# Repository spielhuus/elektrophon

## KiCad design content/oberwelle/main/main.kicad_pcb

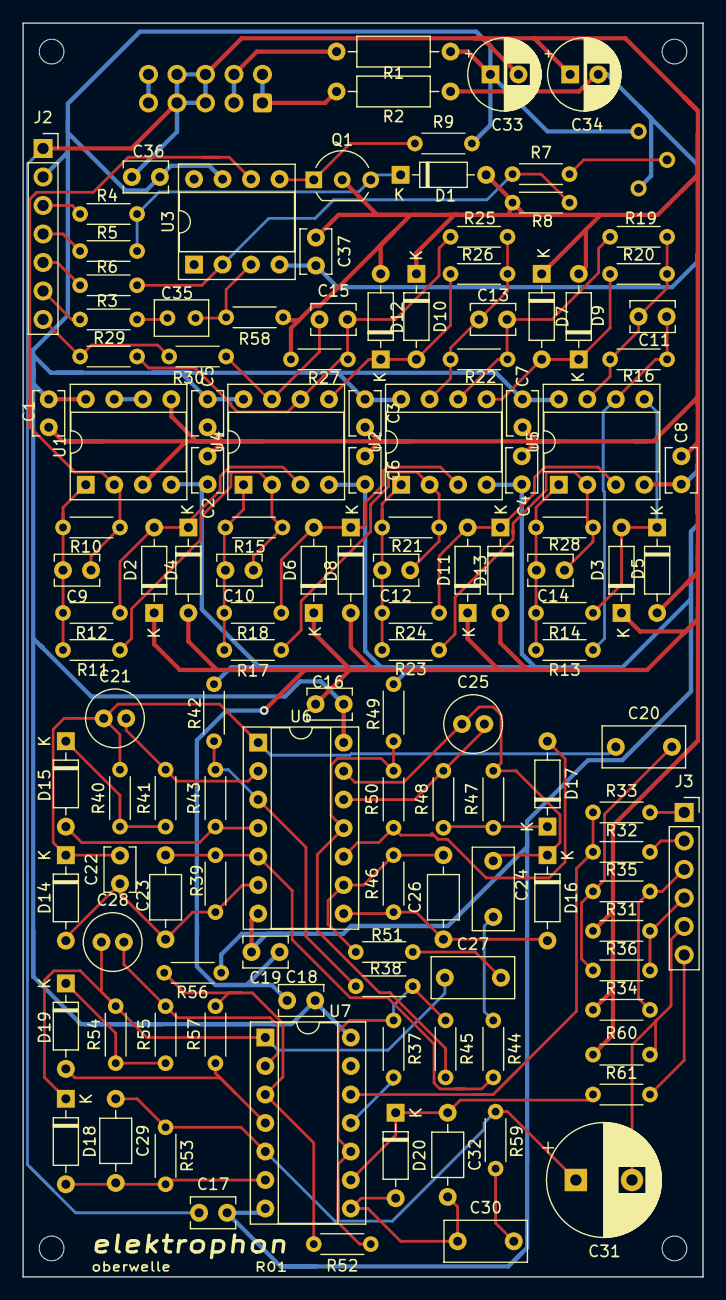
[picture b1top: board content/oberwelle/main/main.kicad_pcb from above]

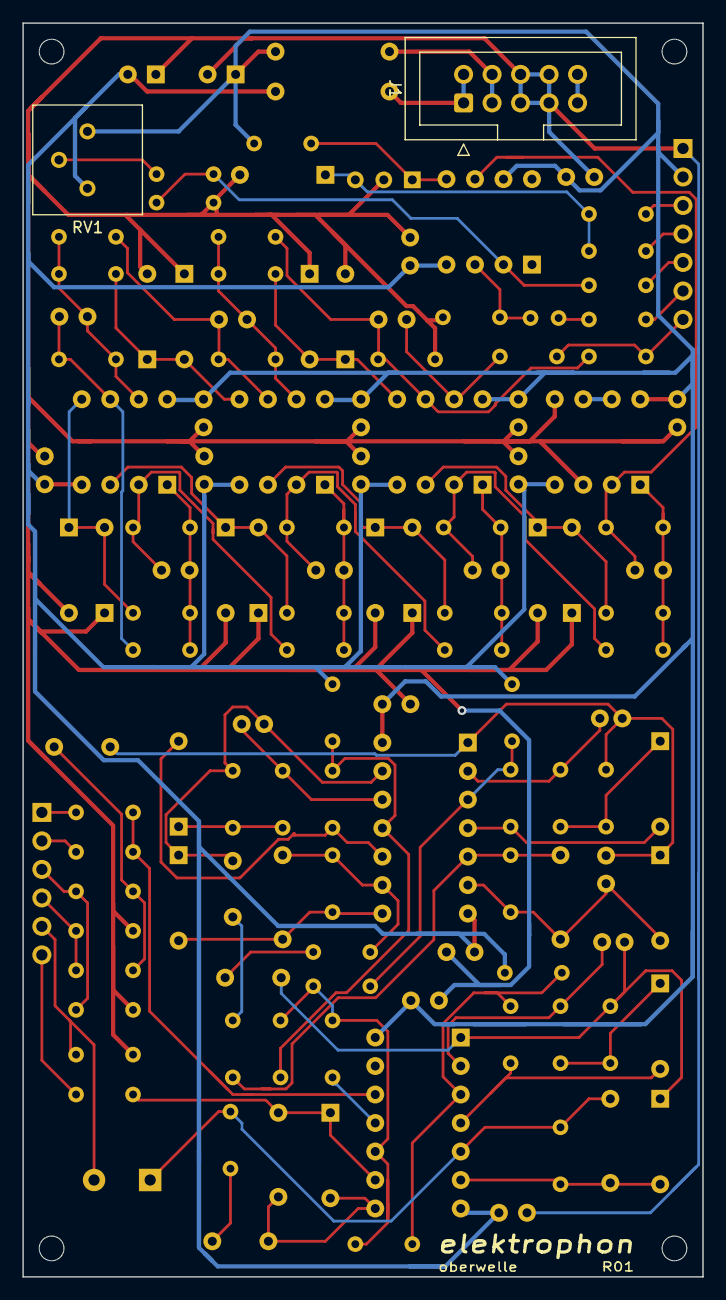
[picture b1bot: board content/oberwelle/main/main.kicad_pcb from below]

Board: 2 copper layers, 60.6 x 111.8 mm, 134 parts (2 on the bottom side), 74 nets.

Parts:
C1, C2, C3, C4, C5, C6, C7, C8, C16, C17, C18, C19, C36, C37: 0.1u; C_Disc_D3.8mm_W2.6mm_P2.50mm
C9: 150p; C_Disc_D3.8mm_W2.6mm_P2.50mm
C10, C11, C12, C13, C14, C15, C22: 47p; C_Disc_D3.8mm_W2.6mm_P2.50mm
C20, C24, C27, C30: 47n; C_Rect_L7.2mm_W3.5mm_P5.00mm_FKS2_FKP2_MKS2_MKP2
C21, C25, C28: 1u (BP); C_Radial_D5.0mm_H11.0mm_P2.00mm
C23, C26, C29, C32: 30p; C_Axial_L3.8mm_D2.6mm_P7.50mm_Horizontal
C31: 47u (BP); CP_Radial_D10.0mm_P5.00mm
C33, C34: 22u; CP_Radial_D6.3mm_P2.50mm
C35: 220n; C_Rect_L4.6mm_W3.0mm_P2.50mm_MKS02_FKP02
D1, D2, D3, D4, D5, D6, D7, D8, D9, D10, D11, D12, D13, D14, D15, D16, D17, D18, D19: 1N4148; D_DO-35_SOD27_P7.62mm_Horizontal
D20: 4.3V/400mW; D_DO-35_SOD27_P7.62mm_Horizontal
J1: IDC Header; IDC-Header_2x05_P2.54mm_Vertical
J2: Conn_01x07_Female; PinSocket_1x07_P2.54mm_Vertical
J3: Conn_01x06_Female; PinSocket_1x06_P2.54mm_Vertical
Q1: BC557; TO-92_Inline_Wide
R1, R2: 10; R_Axial_DIN0207_L6.3mm_D2.5mm_P10.16mm_Horizontal
R3, R6, R11, R13, R15, R16, R17, R19, R21, R22, R23, R25, R28, R29, R31, R33, R34, R59, R60: 100k; R_Axial_DIN0204_L3.6mm_D1.6mm_P5.08mm_Horizontal
R4: 47k; R_Axial_DIN0204_L3.6mm_D1.6mm_P5.08mm_Horizontal
R5: 15k; R_Axial_DIN0204_L3.6mm_D1.6mm_P5.08mm_Horizontal
R7: 3.3meg; R_Axial_DIN0204_L3.6mm_D1.6mm_P5.08mm_Horizontal
R8, R58: 1.5k; R_Axial_DIN0204_L3.6mm_D1.6mm_P5.08mm_Horizontal
R9: 6.8meg; R_Axial_DIN0204_L3.6mm_D1.6mm_P5.08mm_Horizontal
R10: 82k; R_Axial_DIN0204_L3.6mm_D1.6mm_P5.08mm_Horizontal
R12, R14, R18, R20, R24, R26: 33k; R_Axial_DIN0204_L3.6mm_D1.6mm_P5.08mm_Horizontal
R27: 10k; R_Axial_DIN0204_L3.6mm_D1.6mm_P5.08mm_Horizontal
R30: 330; R_Axial_DIN0204_L3.6mm_D1.6mm_P5.08mm_Horizontal
R32, R38: 220k; R_Axial_DIN0204_L3.6mm_D1.6mm_P5.08mm_Horizontal
R35, R36, R43, R44, R51: 1meg; R_Axial_DIN0204_L3.6mm_D1.6mm_P5.08mm_Horizontal
R37: 150k; R_Axial_DIN0204_L3.6mm_D1.6mm_P5.08mm_Horizontal
R39, R46, R53, R57: 2.2meg; R_Axial_DIN0204_L3.6mm_D1.6mm_P5.08mm_Horizontal
R40, R41, R47, R48, R54, R55: 10meg; R_Axial_DIN0204_L3.6mm_D1.6mm_P5.08mm_Horizontal
R42, R49, R56: 820k; R_Axial_DIN0204_L3.6mm_D1.6mm_P5.08mm_Horizontal
R45: 330k; R_Axial_DIN0204_L3.6mm_D1.6mm_P5.08mm_Horizontal
R50: 1.5meg; R_Axial_DIN0204_L3.6mm_D1.6mm_P5.08mm_Horizontal
R52: 470k; R_Axial_DIN0204_L3.6mm_D1.6mm_P5.08mm_Horizontal
R61: 3.3k; R_Axial_DIN0204_L3.6mm_D1.6mm_P5.08mm_Horizontal
REF1, REF2, REF3, REF4: MountingHole_2.2mm_M2
RV1: 100k; Potentiometer_Bourns_3386P_Vertical
U1, U2, U4, U5: TL072; DIP-8_W7.62mm_Socket
U3: CA3080; DIP-8_W7.62mm_Socket
U6, U7: LM3900; DIP-14_W7.62mm_Socket

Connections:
+5V: J1.9, J1.10
+15V: C1.1, C3.1, C5.1, C7.1, C16.1, C18.1, C33.1, C36.1, J2.2, R1.1, R9.2, RV1.1, U1.8, U2.8, U3.7, U4.8, U5.8, U6.14, U7.14
-15V: C2.2, C4.2, C6.2, C8.2, C17.2, C19.2, C34.2, C37.2, R2.1, R42.1, R49.1, R56.1, RV1.3, U1.4, U2.4, U3.4, U4.4, U5.4, U6.7, U7.7
CV: J3.1, R33.2
CV_INITIAL: J3.2, R32.2
GND: C1.2, C2.1, C3.2, C4.1, C5.2, C6.1, C7.2, C8.1, C16.2, C17.1, C18.2, C19.1, C33.2, C34.1, C36.2, C37.1, D1.2, D2.1, D3.1, D4.2, D5.2, D6.1, D7.1, D8.2, D9.2, D10.1, D11.1, D12.2, D13.2, J1.5, J1.6, J1.7, J1.8, J2.1, Q1.2, R8.1, R27.1, R31.1, R34.1, R58.1, R60.1, U1.3, U1.5
IN_1: J3.3, R34.2, R35.2
IN_2: J3.4, R31.2, R36.2
M_CV: J2.4, R5.2
M_CV_INITIAL: J2.3, R4.2
M_IN_1: J2.6, R3.2
M_IN_2: J2.5, R6.2
M_OUT: J2.7, R29.1, R30.1
unnamed: C9.1, R10.1, R11.2, R12.2, U1.1
unnamed: C9.2, R10.2, U1.2, U3.6
unnamed: C10.1, R15.1, R17.2, R18.2, U4.1
unnamed: C10.2, R11.1, R15.2, U4.2
unnamed: C11.1, R16.1, R19.2, R20.2, U5.7
unnamed: C11.2, R13.1, R16.2, U5.6
unnamed: C12.1, R21.1, R23.2, R24.2, U2.1
unnamed: C12.2, R17.1, R21.2, U2.2
unnamed: C13.1, R22.1, R25.2, R26.2, U2.7
unnamed: C13.2, R19.1, R22.2, U2.6
unnamed: C14.1, R13.2, R14.2, R28.1, U5.1
unnamed: C14.2, R23.1, R28.2, U5.2
unnamed: C15.1, R30.2, U4.7
unnamed: C15.2, R25.1, R27.2, R29.2, U4.6
unnamed: C20.1, C21.1, C22.2, D14.1, R40.2, U6.1
unnamed: C20.2, R35.1, R36.1
unnamed: C21.2, R41.2, U6.2
unnamed: C22.1, C23.2, D14.2, R39.2, U6.6
unnamed: C23.1, R39.1, R44.2, U6.5
unnamed: C24.1, C25.1, D16.1, R47.2, U6.13
unnamed: C24.2, R44.1
unnamed: C25.2, R48.2, U6.12
unnamed: C26.1, R46.1, R51.2, U6.9
unnamed: C26.2, D16.2, R46.2, U6.8
unnamed: C27.1, C28.1, D18.1, R54.2, U7.1
unnamed: C27.2, R51.1
unnamed: C28.2, R55.2, U7.2
unnamed: C29.1, C31.1, R53.1, R59.2, U7.5
unnamed: C29.2, D18.2, R53.2, U7.6
unnamed: C30.1, C32.2, D20.2, U7.8
unnamed: C30.2, R59.1
unnamed: C32.1, D20.1, R61.1, U7.9
unnamed: C35.1, R58.2, U3.3
unnamed: C35.2, R3.1
unnamed: D1.1, Q1.3, R4.1, R5.1
unnamed: D2.2, D4.1, R12.1, U4.3
unnamed: D3.2, D5.1, R14.1, U5.5
unnamed: D6.2, D8.1, R18.1, U2.3
unnamed: D7.2, D9.1, R20.1, U2.5
unnamed: D10.2, D12.1, R26.1, U4.5
unnamed: D11.2, D13.1, R24.1, U5.3
unnamed: D15.1, R40.1, R41.1
unnamed: D15.2, R43.1, U6.4
unnamed: D17.1, R47.1, R48.1
unnamed: D17.2, R50.1, U6.10
unnamed: D19.1, R54.1, R55.1
unnamed: D19.2, R57.1, U7.4
unnamed: Q1.1, R9.1, U3.5
unnamed: R6.1, R7.1, R8.2, U3.2
unnamed: R7.2, RV1.2
unnamed: R32.1, R33.1, U7.12
unnamed: R37.1, R38.1, R45.1, R52.1, U7.10
unnamed: R37.2, U7.11
unnamed: R38.2, R42.2, R43.2, U6.3
unnamed: R45.2, R49.2, R50.2, U6.11
unnamed: R52.2, R56.2, R57.2, U7.3
unnamed: U1.6, U1.7
OUT_1: C31.2, J3.5, R60.2
OUT_2: J3.6, R61.2
VN: J1.1, J1.2, R2.2
VP: J1.3, J1.4, R1.2

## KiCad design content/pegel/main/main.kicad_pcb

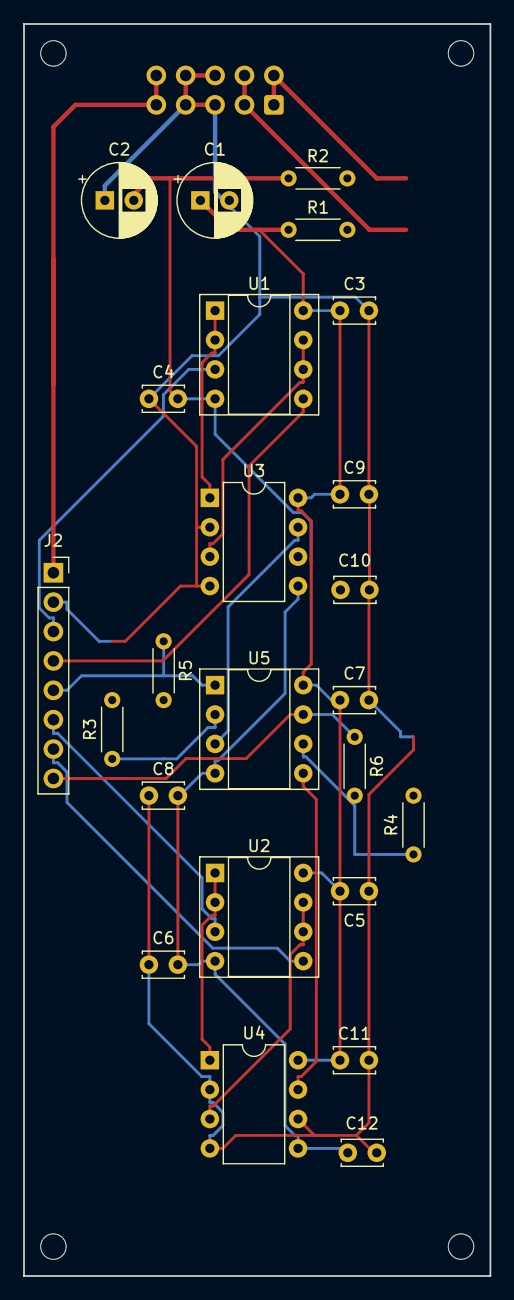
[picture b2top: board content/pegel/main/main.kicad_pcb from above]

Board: 2 copper layers, 40.3 x 108.2 mm, 29 parts (1 on the bottom side), 20 nets.

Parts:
C1, C2: 22u; CP_Radial_D6.3mm_P2.50mm
C3, C4, C5, C6, C7, C8, C9, C10, C11, C12: 0.1u; C_Disc_D3.4mm_W2.1mm_P2.50mm
H1, H2, H3, H4: MountingHole; MountingHole_2.2mm_M2
J1: IDC Header; IDC-Header_2x05_P2.54mm_Vertical
J2: Conn_01x08_Female; PinSocket_1x08_P2.54mm_Vertical
R1, R2: 10; R_Axial_DIN0204_L3.6mm_D1.6mm_P5.08mm_Horizontal
R3, R4, R5, R6: 10k; R_Axial_DIN0204_L3.6mm_D1.6mm_P5.08mm_Horizontal
U1, U2, U5: OPA2134; DIP-8_W7.62mm_Socket
U3, U4: AD633; DIP-8_W7.62mm

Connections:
+5V: J1.9, J1.10, J2.1
+15V: C1.1, C3.1, C5.1, C7.1, C9.1, C11.1, R1.1, U1.8, U2.8, U3.8, U4.8, U5.8
-15V: C2.2, C4.2, C6.2, C8.2, C10.2, C12.2, R2.1, U1.4, U2.4, U3.5, U4.5, U5.4
GND: C1.2, C2.1, C3.2, C4.1, C5.2, C6.1, C7.2, C8.1, C9.2, C10.1, C11.2, C12.1, J1.5, J1.6, J1.7, J1.8, J2.2, R3.2, R4.2, U3.2, U3.4, U3.6, U4.2, U4.4, U4.6
unnamed: R3.1, R5.2, U5.2
unnamed: R4.1, R6.2, U5.6
unnamed: U1.1, U1.2, U3.1
unnamed: U1.6, U1.7, U3.3
unnamed: U2.1, U2.2, U4.1
unnamed: U2.6, U2.7, U4.3
unnamed: U3.7, U5.3
unnamed: U4.7, U5.5
OUTa: J2.5, R5.1, U5.1
OUTb: J2.8, R6.1, U5.7
VN: J1.1, J1.2, R2.2
VP: J1.3, J1.4, R1.2
Xa: J2.3, U1.3
Xb: J2.6, U2.3
Ya: J2.4, U1.5
Yb: J2.7, U2.5

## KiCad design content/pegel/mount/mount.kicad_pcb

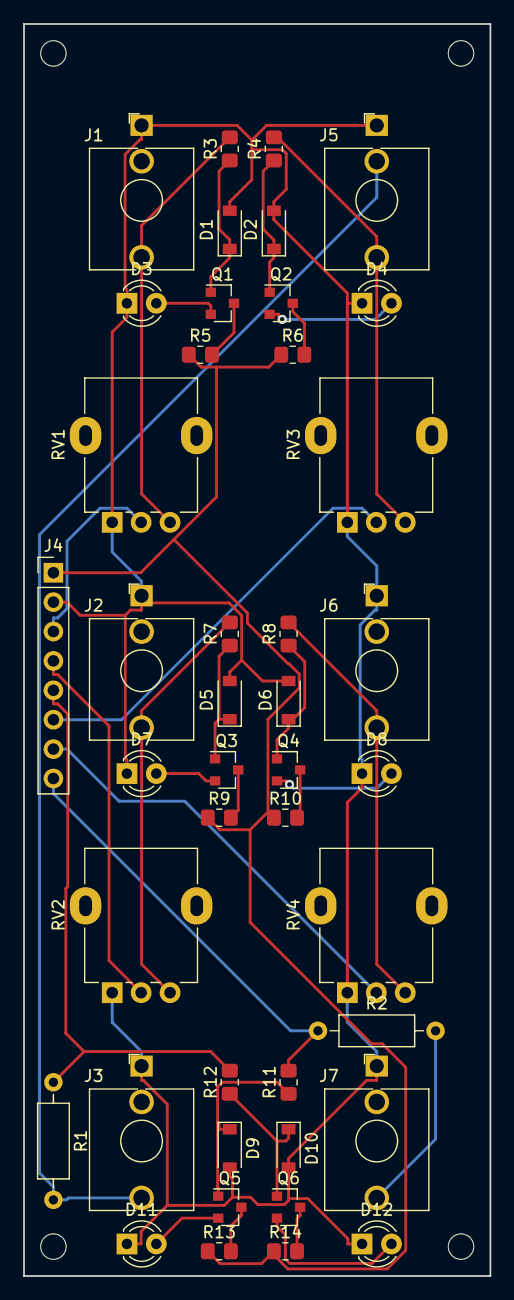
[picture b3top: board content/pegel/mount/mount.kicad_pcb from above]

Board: 2 copper layers, 40.3 x 108.2 mm, 47 parts (0 on the bottom side), 32 nets.

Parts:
D1, D2, D5, D6, D9, D10: 1N4148W; D_SOD-123
D3, D4, D7, D8, D11, D12: LED; LED_D3.0mm
H1, H2, H3, H4: MountingHole; MountingHole_2.2mm_M2
J1, J5: IN_X; Jack_3.5mm_WQP-PJ398SM_Vertical
J2, J6: IN_Y; Jack_3.5mm_WQP-PJ398SM_Vertical
J3, J7: OUT; Jack_3.5mm_WQP-PJ398SM_Vertical
J4: Conn_01x08_Male; PinHeader_1x08_P2.54mm_Vertical
Q1, Q2, Q3, Q4, Q5, Q6: MMBT3904; SOT-23
R1, R2: 1k; R_Axial_DIN0207_L6.3mm_D2.5mm_P10.16mm_Horizontal
R3, R4, R7, R8, R11, R12: 100k; R_0805_2012Metric_Pad1.20x1.40mm_HandSolder
R5, R6, R9, R10, R13, R14: 5k; R_0805_2012Metric_Pad1.20x1.40mm_HandSolder
RV1, RV2, RV3, RV4: 100k; Potentiometer_Alpha_RD901F-40-00D_Single_Vertical

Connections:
+5V: J4.1, R5.1, R6.1, R9.1, R10.1, R13.1, R14.1
/IN1x: J1.T, R3.2, RV1.3
/IN1y: J2.T, R7.2, RV2.3
/IN2x: J5.T, R4.2, RV3.3
/IN2y: J6.T, R8.2, RV4.3
GND: D1.2, D2.2, D3.1, D4.1, D5.2, D6.2, D7.1, D8.1, D9.2, D10.2, D11.1, D12.1, J1.S, J2.S, J3.S, J4.2, J5.S, J6.S, J7.S, RV1.1, RV2.1, RV3.1, RV4.1
unnamed: D1.1, Q1.1, R3.1
unnamed: D2.1, Q2.1, R4.1
unnamed: D3.2, Q1.2
unnamed: D4.2, Q2.2
unnamed: D5.1, Q3.1, R7.1
unnamed: D6.1, Q4.1, R8.1
unnamed: D7.2, Q3.2
unnamed: D8.2, Q4.2
unnamed: D9.1, Q5.1, R11.1
unnamed: D10.1, Q6.1, R12.1
unnamed: D11.2, Q5.2
unnamed: D12.2, Q6.2
unnamed: J3.T, J5.TN, R1.2
unnamed: J7.T, R2.2
unnamed: Q1.3, R5.2
unnamed: Q2.3, R6.2
unnamed: Q3.3, R9.2
unnamed: Q4.3, R10.2
unnamed: Q5.3, R13.2
unnamed: Q6.3, R14.2
OUTa: J4.5, R1.1, R12.2
OUTb: J4.8, R2.1, R11.2
Xa: J4.3, RV1.2
Xb: J4.6, RV3.2
Ya: J4.4, RV2.2
Yb: J4.7, RV4.2

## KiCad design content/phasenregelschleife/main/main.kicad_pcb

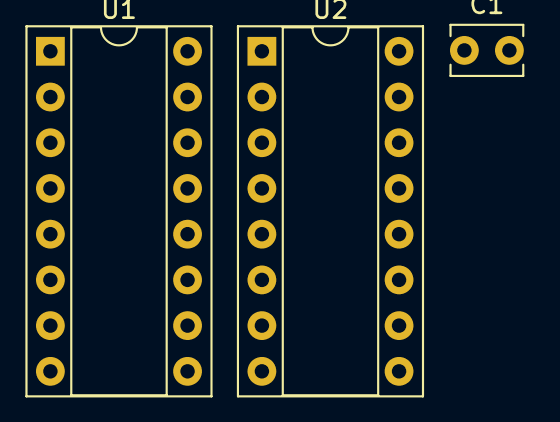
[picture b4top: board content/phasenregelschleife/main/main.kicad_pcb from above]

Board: 2 copper layers, 3 parts (0 on the bottom side), 3 nets, no tracks yet.

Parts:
C1: 0.01u; C_Disc_D3.8mm_W2.6mm_P2.50mm
U1, U2: 4046; DIP-16_W7.62mm_Socket

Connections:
GND: U1.5, U1.8
unnamed: C1.1, U1.6
unnamed: C1.2, U1.7

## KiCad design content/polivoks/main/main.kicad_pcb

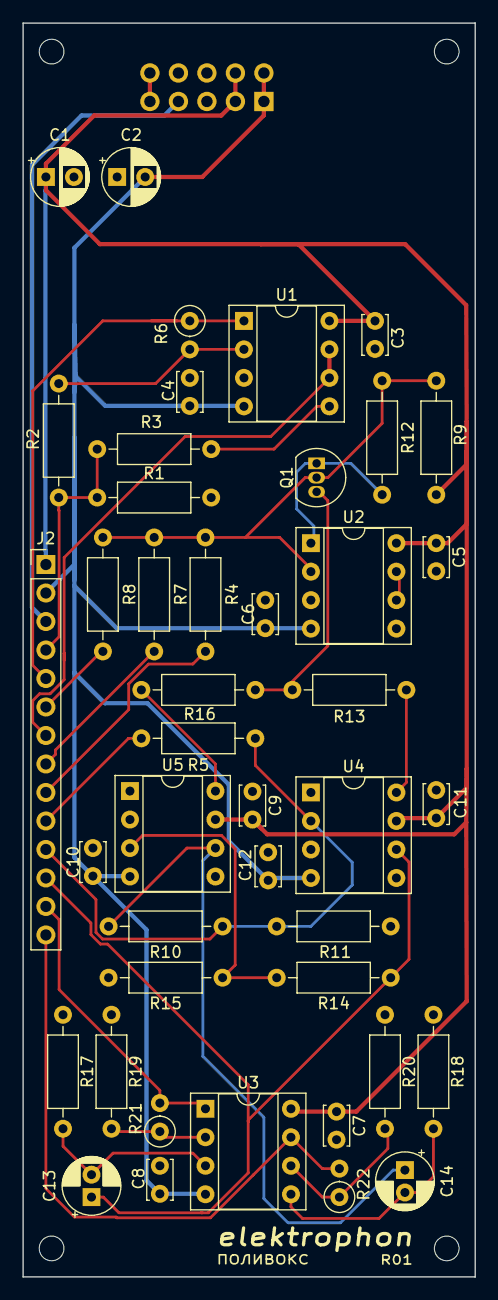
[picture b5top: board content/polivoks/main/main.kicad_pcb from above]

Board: 2 copper layers, 40.3 x 111.8 mm, 48 parts (1 on the bottom side), 29 nets.

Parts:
C1, C2: 10u; CP_Radial_D5.0mm_P2.50mm
C3, C4, C5, C6, C7, C8, C9, C10, C11, C12: 0.1u; C_Disc_D3.4mm_W2.1mm_P2.50mm
C13, C14: 1u; CP_Radial_D5.0mm_P2.00mm
H1, H2, H3, H4: MountingHole; MountingHole_2.2mm_M2
J1: IDC Header; IDC-Header_2x05_P2.54mm_Vertical
J2: Conn_01x14_Female; PinHeader_1x14_P2.54mm_Vertical
Q1: 2N3904; TO-92_Inline
R1: 220k; R_Axial_DIN0207_L6.3mm_D2.5mm_P10.16mm_Horizontal
R2, R4, R9, R17, R18: 100k; R_Axial_DIN0207_L6.3mm_D2.5mm_P10.16mm_Horizontal
R3, R19, R20: 10k; R_Axial_DIN0207_L6.3mm_D2.5mm_P10.16mm_Horizontal
R5: 470k; R_Axial_DIN0207_L6.3mm_D2.5mm_P10.16mm_Horizontal
R6, R21, R22: 100k; R_Axial_DIN0207_L6.3mm_D2.5mm_P2.54mm_Vertical
R7: 162k; R_Axial_DIN0207_L6.3mm_D2.5mm_P10.16mm_Horizontal
R8: 120k; R_Axial_DIN0207_L6.3mm_D2.5mm_P10.16mm_Horizontal
R10, R14: 47k; R_Axial_DIN0207_L6.3mm_D2.5mm_P10.16mm_Horizontal
R11, R15: 1k; R_Axial_DIN0207_L6.3mm_D2.5mm_P10.16mm_Horizontal
R12: 3k; R_Axial_DIN0207_L6.3mm_D2.5mm_P10.16mm_Horizontal
R13, R16: 1M2; R_Axial_DIN0207_L6.3mm_D2.5mm_P10.16mm_Horizontal
U1, U2, U3: TL072; DIP-8_W7.62mm_Socket
U4, U5: LM4250; DIP-8_W7.62mm_Socket

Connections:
+5V: J1.9, J1.10
+15V: C1.1, C3.1, C5.1, C7.1, C9.1, C11.1, J1.3, J1.4, J2.1, R9.2, U1.8, U2.8, U3.8, U4.7, U5.7
-15V: C2.2, C4.2, C6.2, C8.2, C10.2, C12.2, J1.1, J1.2, J2.2, U1.4, U2.4, U3.4, U4.4, U5.4
/bp_out: J2.13, R21.2, U3.1
/cv: J2.9, R4.2
/fm_in: J2.4, R1.2, R2.2, R3.2
/fm_level_1: J2.7, U1.6, U1.7
/fm_level_2: J2.6, R8.2
/fm_level_3: J2.5, R6.1, U1.1
/freq: J2.8, R7.2
/in: J2.10, R5.2
/lp_out: J2.14, R22.2, U3.7
/res_1: J2.11, R5.1, R10.1, R11.2, U4.2
/res_2: C13.1, J2.12, R14.2, U4.6
GND: C1.2, C2.1, C3.2, C4.1, C5.2, C6.1, C7.2, C8.1, C9.2, C10.1, C11.2, C12.1, J1.5, J1.6, J1.7, J1.8, J2.3, R1.1, R11.1, R15.1, R17.1, R18.1, R19.1, R20.1, U1.3, U2.3, U2.5, U4.3, U5.2
unnamed: C13.2, R17.2, U3.3
unnamed: C14.1, R10.2, U5.6
unnamed: C14.2, R18.2, U3.5
unnamed: Q1.1, R12.1, U2.1
unnamed: Q1.2, R4.1, R7.1, R8.1, R9.1, R12.2, U2.2
unnamed: Q1.3, R13.2, R16.2
unnamed: R2.1, R6.2, U1.2
unnamed: R3.1, U1.5
unnamed: R13.1, U4.8
unnamed: R14.1, R15.2, U5.3
unnamed: R16.1, U5.8
unnamed: R19.2, R21.1, U3.2
unnamed: R20.2, R22.1, U3.6
unnamed: U2.6, U2.7

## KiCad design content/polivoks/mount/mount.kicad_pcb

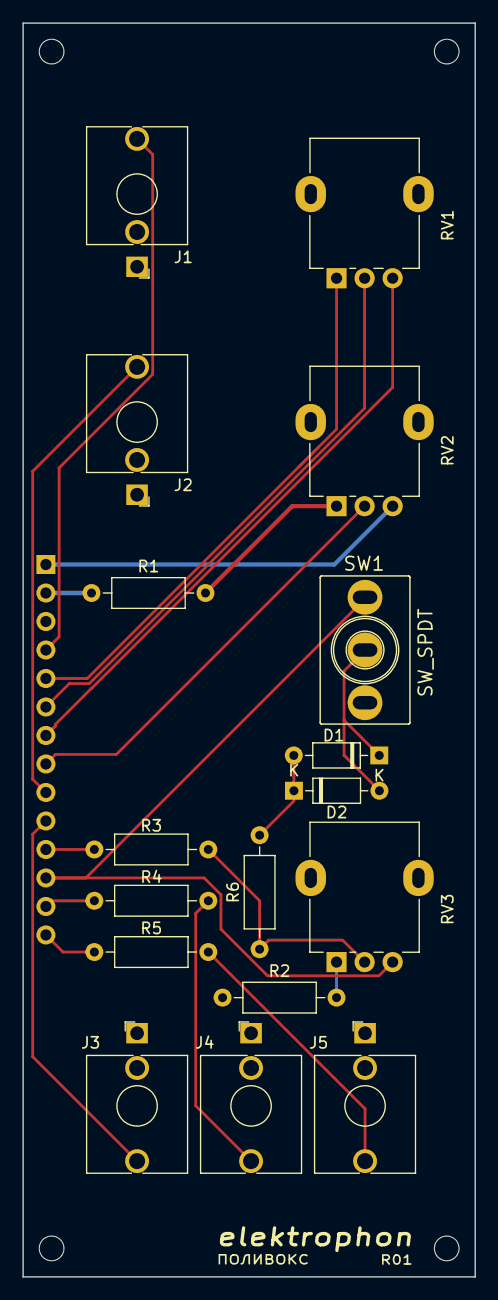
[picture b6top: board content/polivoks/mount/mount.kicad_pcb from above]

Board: 2 copper layers, 40.3 x 111.8 mm, 22 parts (1 on the bottom side), 21 nets.

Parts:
D1, D2: 1N4148; D_DO-35_SOD27_P7.62mm_Horizontal
H1, H2, H3, H4: MountingHole; MountingHole_2.2mm_M2
J1: FM_IN; Jack_3.5mm_WQP-PJ398SM_Vertical
J2: CV_IN; Jack_3.5mm_WQP-PJ398SM_Vertical
J3: INPUT; Jack_3.5mm_WQP-PJ398SM_Vertical
J4: BP_OUT; Jack_3.5mm_WQP-PJ398SM_Vertical
J5: LP_OUT; Jack_3.5mm_WQP-PJ398SM_Vertical
J6: Conn_01x14_Male; PinHeader_1x14_P2.54mm_Vertical
R1: 47k; R_Axial_DIN0207_L6.3mm_D2.5mm_P10.16mm_Horizontal
R2: 100; R_Axial_DIN0207_L6.3mm_D2.5mm_P10.16mm_Horizontal
R3: 27k; R_Axial_DIN0207_L6.3mm_D2.5mm_P10.16mm_Horizontal
R4, R5: 1k; R_Axial_DIN0207_L6.3mm_D2.5mm_P10.16mm_Horizontal
R6: 470; R_Axial_DIN0207_L6.3mm_D2.5mm_P10.16mm_Horizontal
RV1: 47k; Potentiometer_Alpha_RD901F-40-00D_Single_Vertical
RV2, RV3: 100k; Potentiometer_Alpha_RD901F-40-00D_Single_Vertical
SW1: SW_SPDT; SPDT_KIT

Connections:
+15V: J6.1, RV2.3
-15V: J6.2, R1.1
/bp_out: J6.13, R4.1
/cv: J2.T, J6.9
/fm_in: J1.T, J6.4
/fm_level_1: J6.7, RV1.3
/fm_level_2: J6.6, RV1.2
/fm_level_3: J6.5, RV1.1
/freq: J6.8, RV2.2
/in: J3.T, J6.10
/lp_out: J6.14, R5.1
/res_1: J6.11, R3.1
/res_2: J6.12, RV3.3, SW1.1
GND: J1.S, J2.S, J3.S, J4.S, J5.S, J6.3, R2.1
unnamed: D1.1, D2.2, SW1.2
unnamed: D1.2, D2.1, R6.2
unnamed: J4.T, R4.2
unnamed: J5.T, R5.2
unnamed: R1.2, RV2.1
unnamed: R2.2, RV3.1
unnamed: R3.2, R6.1, RV3.2

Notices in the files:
content/oberwelle/main/main.kicad_pcb:
License CC BY 4.0 - Attribution 4.0 International
